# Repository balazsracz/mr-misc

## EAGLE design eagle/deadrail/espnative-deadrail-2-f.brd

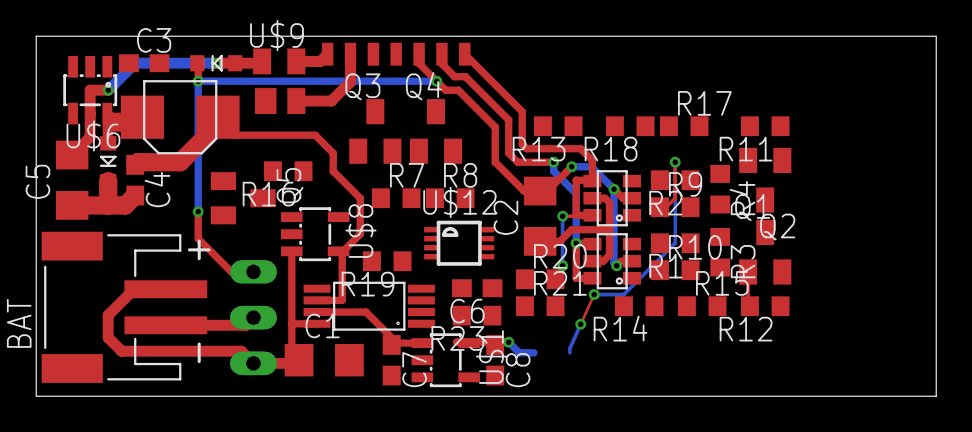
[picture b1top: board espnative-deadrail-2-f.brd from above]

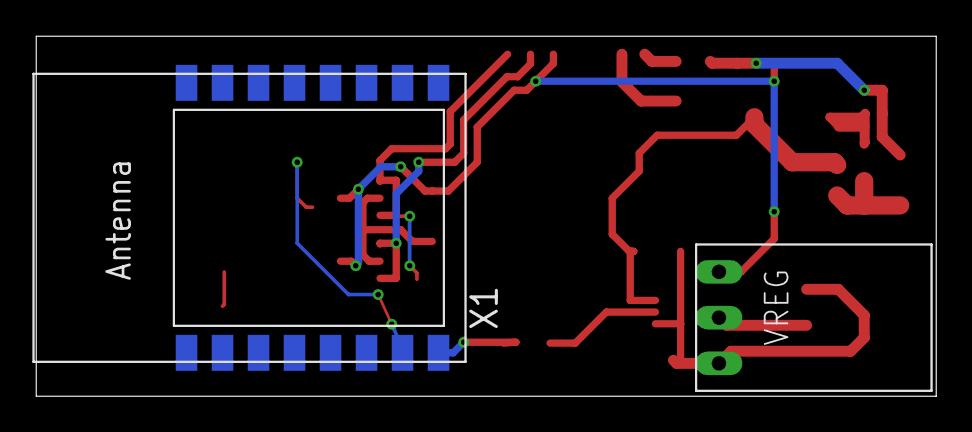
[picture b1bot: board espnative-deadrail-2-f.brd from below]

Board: 2 copper layers, 50.0 x 20.0 mm, 48 parts (2 on the bottom side), 36 nets.

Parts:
BAT: JST-PH-2-SMT-RA
C1, C2: C1206
C3, C7, C8: 1 uF; C0603
C4: 22uF; C0603
C5: 22uF; C1206
C6: 10n; C0603
L1: 10uH; FDSD0420
Q1, Q2, Q3, Q4, Q5: BSS123; SOT23
R1, R2: 5k; R0603
R3, R4, R13, R15, R17, R18: 10k; R0603
R7, R9, R10, R11, R12, R14: 47k; R0603
R8: 270k; R0603
R16: 2k2; R0603
R19: 500; R0603
R20, R21: 15k; R0603
R23: 1k..5k; R0603
U$1: AP2112K-3V3; SOT23-5L
U$2, U$3: DMG6601-LVT; TSOT-26
U$4: TPS2115A; TSSOP-8
U$5: POLOLU-VREG12; POLOLU-REGULATOR
U$6: LMR16006Y; SOT23-6
U$7, U$11: DIODE; DIODE-1206
U$8: STC4054; SOT23-5L
U$9: BAS3007A; SOT143B
U$10: DECODER-WIRE-PADS7; DECODER-WIRE-PADS
U$12: TS5A3359; US8
X1: ESP-12

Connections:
+3V3: C8.1, R15.1, R17.1, R18.1, U$1.5, U$12.8, X1.8
+4.1V: C7.1, U$1.1, U$1.3, U$4.7
+5V: C4.1, L1.P$1, U$4.6, U$6.3, U$8.4
+12V: C2.2, R1.2, R2.2, U$2.2, U$3.2, U$5.VOUT, U$10.3, U$11.C
BAT_EN: R14.1, U$4.2, X1.4
CHRG_EN: Q5.1, R13.1, X1.10
CHRG_FB: R16.1, U$8.5, U$12.2
DCC_VPLUS: C5.2, U$6.5, U$9.4, U$11.A
F0_FRONT: Q3.1, X1.15
F0_REAR: Q4.1, X1.13
GND: BAT.2, C1.2, C2.1, C4.2, C5.1, C6.2, C7.2, C8.2, Q1.2, Q2.2, Q3.2, Q4.2, Q5.2, R8.2, R9.2, R10.2, R11.2, R12.1, R13.2, R14.2, R19.2, R23.2, U$1.2, U$2.5, U$3.5, U$4.3, U$4.5, U$5.GND, U$6.2, U$7.C, U$8.2, U$9.1, U$12.4, X1.9
LIGHT_B: Q4.3, U$10.4
LIGHT_F: Q3.3, U$10.5
MOTA_HIGH: Q1.1, R12.2, X1.5
MOTA_LOW: R10.1, U$2.1, X1.6
MOTB_HIGH: Q2.1, R11.1, X1.14
MOTB_LOW: R9.1, U$3.1, X1.7
MOT_A: R21.2, U$2.4, U$2.6, U$10.2
MOT_B: R20.2, U$3.4, U$3.6, U$10.1
MOT_FB: C6.1, R20.1, R21.1, R23.1, U$12.3
unnamed: U$12.7, X1.2
unnamed: R1.1, R3.1, U$2.3
unnamed: Q2.3, R4.2
unnamed: R2.1, R4.1, U$3.3
unnamed: C3.2, L1.P$2, U$6.6, U$7.A
unnamed: Q1.3, R3.2
unnamed: C3.1, U$6.1
unnamed: Q5.3, R16.2
unnamed: R17.2, U$12.6, X1.12
unnamed: R15.2, X1.3
unnamed: R18.2, U$12.5, X1.11
unnamed: R19.1, U$4.4
TRK_L: U$9.3, U$10.7
TRK_R: U$9.2, U$10.6
VBAT: BAT.1, C1.1, R7.1, U$4.8, U$5.VIN, U$8.3
VBAT_FB: R7.2, R8.1, U$12.1

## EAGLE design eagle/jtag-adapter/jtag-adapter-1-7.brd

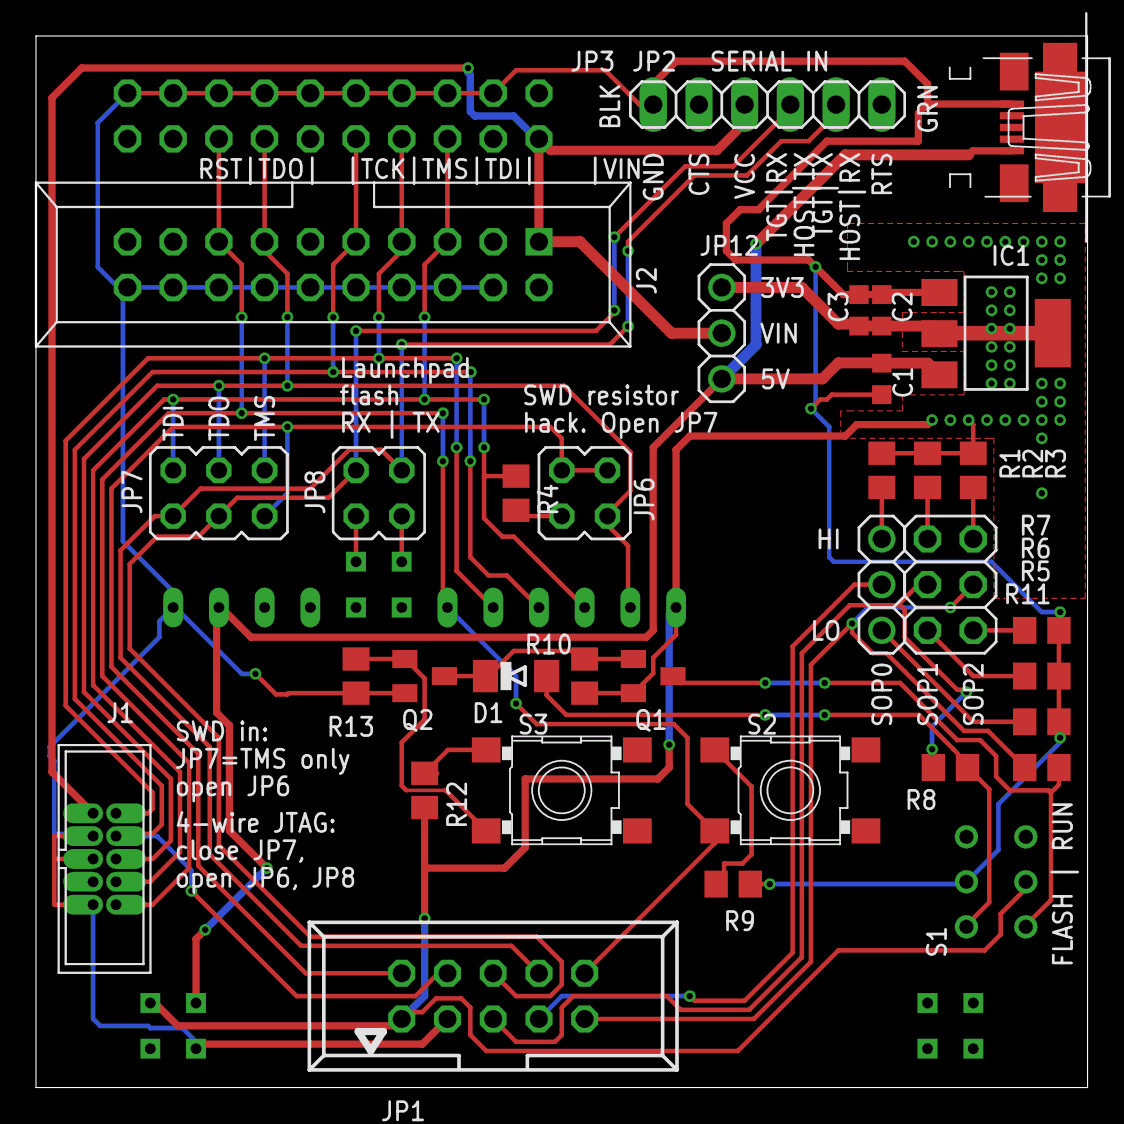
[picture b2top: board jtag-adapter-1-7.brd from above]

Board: 2 copper layers, 58.4 x 58.4 mm, 36 parts (1 on the bottom side), 30 nets.

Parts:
C1, C2: 10u 6.3V; C0603K
C3: 0.1u; C0603K
D1: MINIMELF
IC1: REG1117; SOT223
J1: MA05-2_0.05_X_0.05
J2: MA10-2-SHROUDED
JP1: TAGCONNECT; CON10M
JP2: 1X06
JP3: JTAG-IN; 2X10/90
JP6, JP8: JP2Q
JP7: JP3Q
JP9, JP12: 1X03
JP10: 2X03
JP13: CC3220SF-JTAG-HAT; JTAG-LAUNCHPAD-3220SF
Q1: BSS84; SOT23
Q2: BSS123; SOT23
R1, R2, R3, R5, R6, R7, R8, R9, R11, R12: 270; R0805
R4: 330; R0805
R10, R13: 10k; R0805
S1: DPDT-2.5X3.2MM
S2: RESET; TACTSW-6X6
S3: FLASH; TACTSW-6X6
X1: MICRO-USB-B; MICRO-B-PAC

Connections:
+3V3: C2.1, C3.1, IC1.2, IC1.4, JP1.1, JP12.1, JP13.12-3V3, JP13.16-3V3, Q1.2, R1.2, R2.2, R3.2, R10.1, R12.2, S1.5
+5V: C1.1, IC1.3, JP12.3, JP13.2-5V, JP13.17-5V, X1.1
GND: C1.2, C2.2, C3.2, IC1.1, J1.3, J1.5, J1.9, J2.4, J2.6, J2.8, J2.10, J2.12, J2.14, J2.16, J2.18, J2.20, JP1.3, JP2.1, JP3.4, JP3.6, JP3.8, JP3.10, JP3.12, JP3.14, JP3.16, JP3.18, JP3.20, JP13.1-GND, JP13.19-GND, Q2.2, R5.1, R6.1, R7.1, R9.2, R13.1, S1.2, X1.5
unnamed: R9.1, S2.1
unnamed: JP6.4, R4.2
unnamed: D1.C, Q1.1, Q2.3, R10.2
unnamed: R12.1, S3.1
unnamed: Q2.1, R13.2, S3.3
unnamed: Q1.3, R11.2, S1.4
unnamed: JP8.1, JP13.14-RX
unnamed: JP8.3, JP13.15-TX
unnamed: D1.A, R8.1, S1.1
NRESET: J1.10, J2.15, JP1.10, JP3.15, JP13.7-RESET, S2.3
RX: JP1.6, JP2.4, JP7.3, JP8.2
SOP0: JP1.7, JP9.2
SOP0H: JP9.1, R1.1
SOP0L: JP9.3, R5.2
SOP1: JP1.5, JP10.3, R8.2
SOP1H: JP10.1, R2.1
SOP1L: JP10.5, R6.2
SOP2: JP1.9, JP10.4, R11.1
SOP2H: JP10.2, R3.1
SOP2L: JP10.6, R7.2
SWCLK: J1.4, J2.9, JP1.4, JP3.9, JP13.9-TCK
SWDIO: JP1.2, JP6.1, JP6.3, JP7.5
TDI: J1.8, J2.5, JP3.5, JP7.2, JP13.10-TDI, R4.1
TDO: J1.6, J2.13, JP3.13, JP6.2, JP7.4, JP13.11-TDO
TMS: J1.2, J2.7, JP3.7, JP7.6, JP13.8-TMS
TX: JP1.8, JP2.5, JP7.1, JP8.4
VREF: J1.1, J2.1, JP2.3, JP3.1, JP12.2

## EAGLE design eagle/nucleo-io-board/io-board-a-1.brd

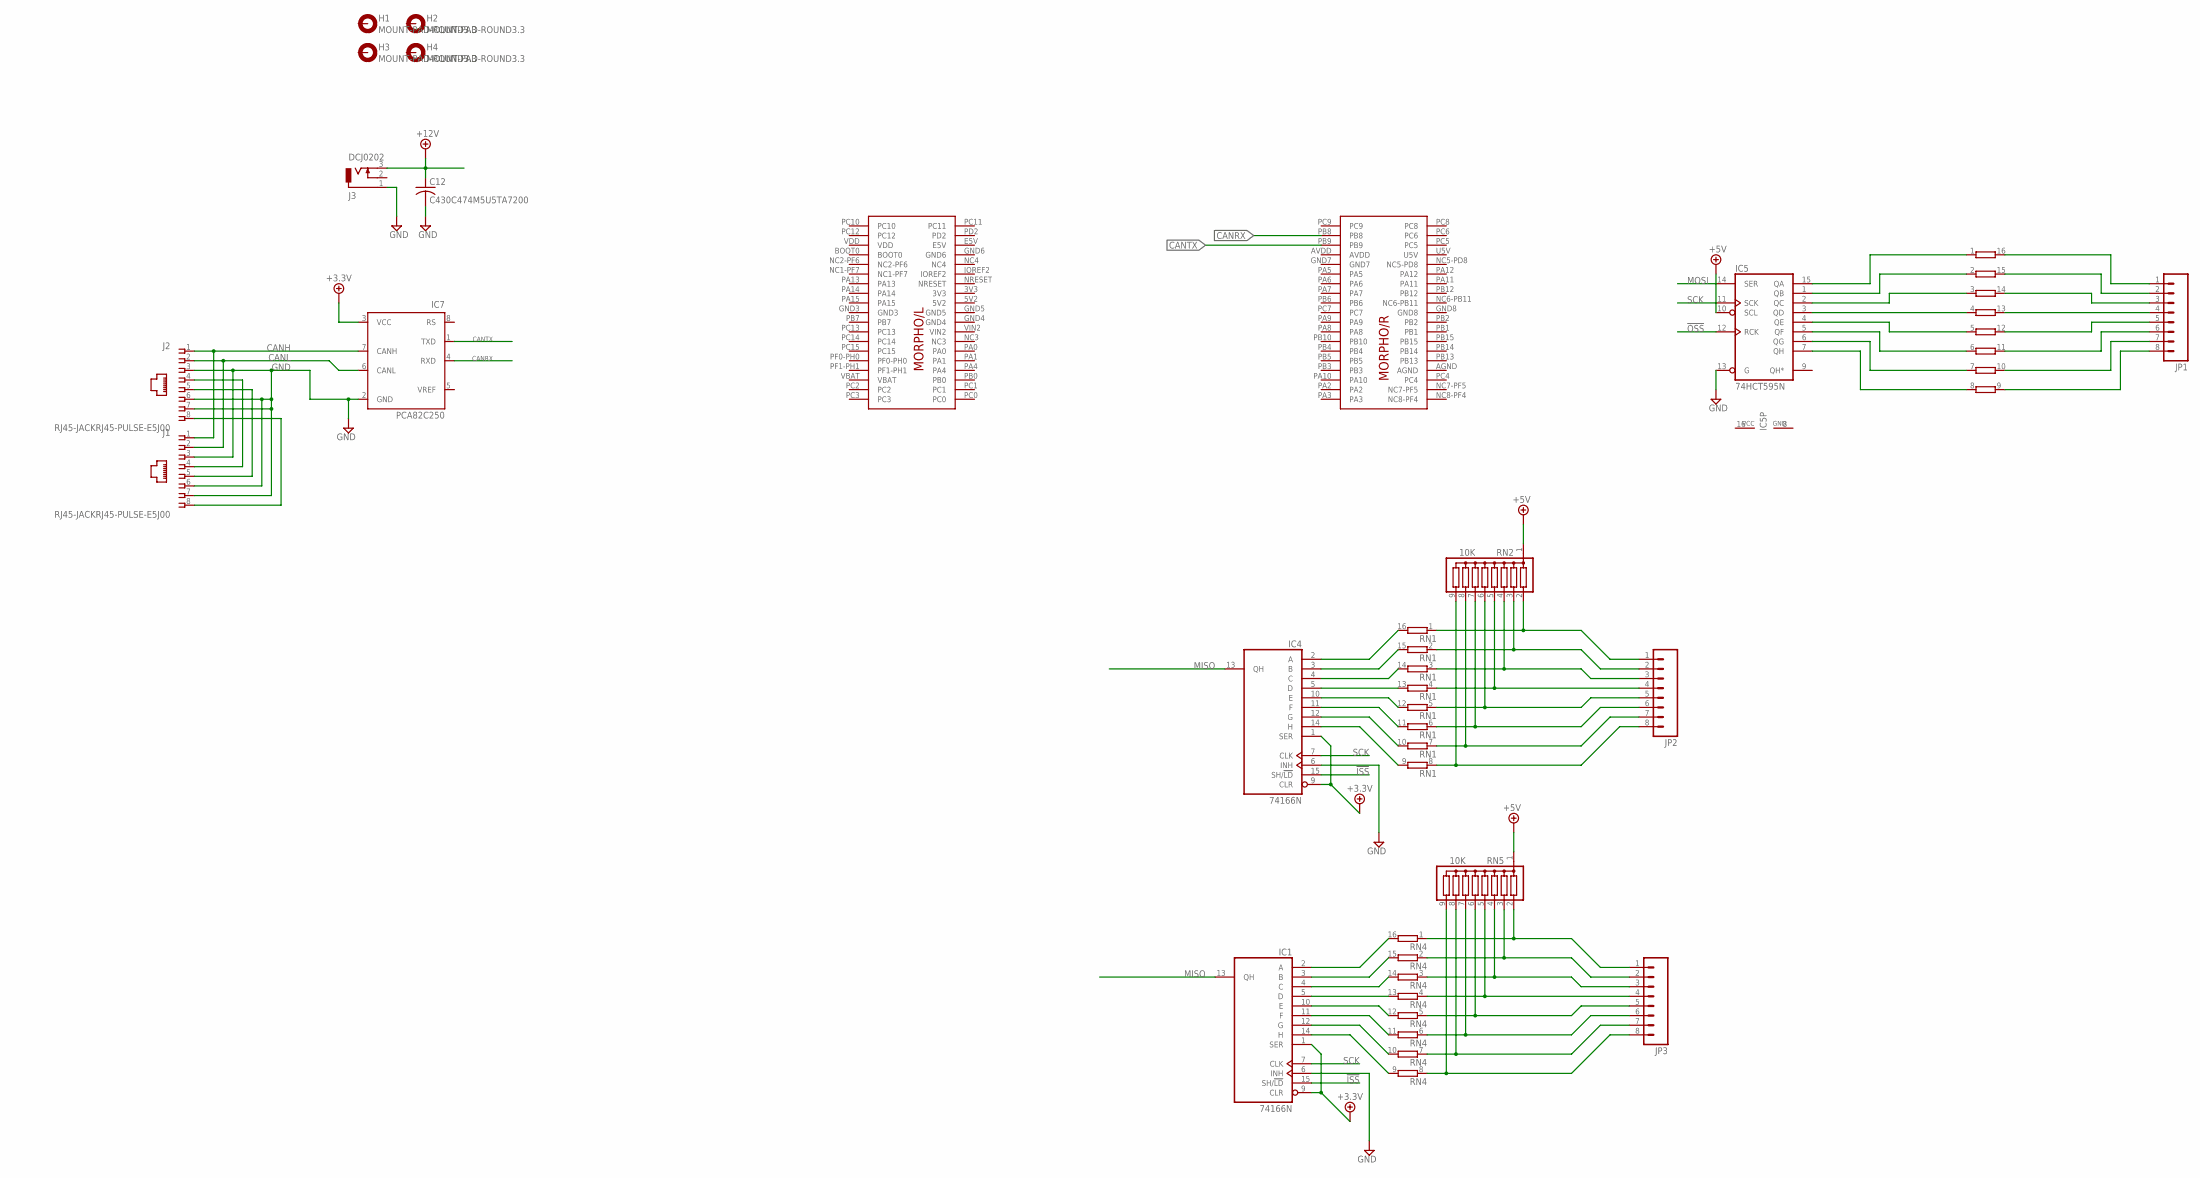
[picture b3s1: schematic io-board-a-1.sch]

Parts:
C12: C430C474M5U5TA7200; C075-032X103
H1, H2, H3, H4: MOUNT-PAD-ROUND3.3; 3,3-PAD
IC1, IC4: 74166N; DIL16
IC5: 74HCT595N; DIL16
IC7: PCA82C250; DIL08
J1, J2: RJ45-JACKRJ45-PULSE-E5J00; RJ45-PULSE-E5J88
J3: DCJ0202
JP1, JP2, JP3: M08LOCK; 1X08_LOCK
RN1, RN3, RN4: 8R-P; DIL16
RN2, RN5: 10K; SIL9
U$1: NUCLEO_64_GENERIC; NUCLEO_BRD_BASE64

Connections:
3V3: U$1.3V3
5V2: U$1.5V2
!ISS: IC1.15 (SH/!LD), IC4.15 (SH/!LD)
!OSS: IC5.12 (RCK)
+3.3V: IC1.1 (SER), IC1.9 (CLR), IC4.1 (SER), IC4.9 (CLR), IC7.3 (VCC)
+5V: IC5.10 (SCL), RN2.1, RN5.1
+12V: C12.1, J3.3
AGND: U$1.AGND
AVDD: U$1.AVDD
CANH: IC7.7 (CANH), J1.1, J2.1
CANL: IC7.6 (CANL), J1.2, J2.2
CANRX: IC7.4 (RXD), U$1.PB8
CANTX: IC7.1 (TXD), U$1.PB9
E5V: U$1.E5V
GND: C12.2, IC1.6 (INH), IC1.8 (GND), IC4.6 (INH), IC4.8 (GND), IC5.8 (GND), IC5.13 (G), IC7.2 (GND), J1.3, J1.6, J1.7, J2.3, J2.6, J2.7, J3.1
GND3: U$1.GND3
GND4: U$1.GND4
GND5: U$1.GND5
GND6: U$1.GND6
GND7: U$1.GND7
GND8: U$1.GND8
MISO: IC1.13 (QH), IC4.13 (QH)
MOSI: IC5.14 (SER)
unnamed: IC5.15 (QA), RN3.1
unnamed: IC5.1 (QB), RN3.2 (1)
unnamed: IC5.2 (QC), RN3.3 (1)
unnamed: J1.4, J2.4
unnamed: J1.5, J2.5
unnamed: JP3.1, RN4.1, RN5.2
unnamed: IC5.3 (QD), RN3.4 (1)
unnamed: IC5.4 (QE), RN3.5 (1)
unnamed: IC5.5 (QF), RN3.6 (1)
unnamed: IC5.6 (QG), RN3.7 (1)
unnamed: IC5.7 (QH), RN3.8 (1)
unnamed: JP1.1, RN3.16 (2)
unnamed: JP1.8, RN3.9 (2)
unnamed: JP3.2, RN4.2 (1), RN5.3
unnamed: JP3.3, RN4.3 (1), RN5.4
unnamed: JP3.4, RN4.4 (1), RN5.5
unnamed: JP1.2, RN3.15 (2)
unnamed: JP1.3, RN3.14 (2)
unnamed: JP3.5, RN4.5 (1), RN5.6
unnamed: JP3.6, RN4.6 (1), RN5.7
unnamed: JP3.7, RN4.7 (1), RN5.8
unnamed: JP3.8, RN4.8 (1), RN5.9
unnamed: IC1.2 (A), RN4.16 (2)
unnamed: IC1.3 (B), RN4.15 (2)
unnamed: JP2.1, RN1.1, RN2.2
unnamed: JP2.2, RN1.2 (1), RN2.3
unnamed: JP2.3, RN1.3 (1), RN2.4
unnamed: JP2.4, RN1.4 (1), RN2.5
unnamed: IC1.4 (C), RN4.14 (2)
unnamed: IC1.5 (D), RN4.13 (2)
unnamed: IC1.10 (E), RN4.12 (2)
unnamed: IC1.11 (F), RN4.11 (2)
unnamed: JP2.5, RN1.5 (1), RN2.6
unnamed: JP2.6, RN1.6 (1), RN2.7
unnamed: JP2.7, RN1.7 (1), RN2.8
unnamed: JP2.8, RN1.8 (1), RN2.9
unnamed: IC1.12 (G), RN4.10 (2)
unnamed: IC1.14 (H), RN4.9 (2)
unnamed: IC4.2 (A), RN1.16 (2)
unnamed: IC4.3 (B), RN1.15 (2)
unnamed: IC4.4 (C), RN1.14 (2)
unnamed: IC4.5 (D), RN1.13 (2)
unnamed: IC4.10 (E), RN1.12 (2)
unnamed: IC4.11 (F), RN1.11 (2)
unnamed: IC4.12 (G), RN1.10 (2)
unnamed: IC4.14 (H), RN1.9 (2)
unnamed: JP1.4, RN3.13 (2)
unnamed: JP1.5, RN3.12 (2)
unnamed: JP1.6, RN3.11 (2)
unnamed: JP1.7, RN3.10 (2)
PWR_POS: J1.8, J2.8
SCK: IC1.7 (CLK), IC4.7 (CLK), IC5.11 (SCK)
U5V: U$1.U5V
VBAT: U$1.VBAT
VCC: IC1.16 (VCC), IC4.16 (VCC), IC5.16 (VCC)
VDD: U$1.VDD
VIN2: U$1.VIN2

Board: 2 copper layers, 21 parts (0 on the bottom side), 63 nets, no tracks yet.
